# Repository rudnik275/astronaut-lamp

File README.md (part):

# Лампа-космонавт → нативное устройство Apple HomeKit

Ночник «космонавт на луне» + звёздный проектор (Rozetka 566431028, AURA_HUB, ~530 грн).
Куплен и разобран 2026-08-23. **Решение: выкидываем ИК-пульт и родной контроллер,
внутрь ставим ESP32-WROOM-32 с прошивкой HAA — лампа появляется в Apple Home как
настоящая цветная LED-лампа + отдельный выключатель проектора, без хабов и мостов.**

## Статус на 2026-09-05 (точка входа для новой сессии)

- ✅ **ESP32 прошит HAA 12.18.1 (04.09)** и **спарен с Home.app**. Чип ESP32-D0WD-V3,
  порт `/dev/cu.usbserial-120`, точка доступа setup-режима `HAA-620DA0`, код спаривания
  `0218-2017`. Имена в Home.app: аксессуар «Космонавт», лампа «Цвет неба», мотор
  «Движение неба». Уровни на GPIO проверены мультиметром: 25 = R, 26 = G, 27 = B, 32 = мотор
- ✅ **С донора выпаяны и промерены** балласты `5R6` (R) и 2× `3R3` (G, B) **плюс `6R8` (R18)**
  из цепи мотора — на доноре мотор шёл `MD → D1 → 6R8 → Q1`, а не напрямую (§1, §3).
  Гнёзда `RGB`/`MD` оказались SMD с шагом 2.0 мм: вилки с кабелей срезаны, кабели теперь
  с голыми концами, провода светодиода опознать по фото вилок
- 📐 **Схема, таблица соединений для breadboard, порядок работ и раскладка в корпус:**
  `docs/schematic.html` (та же страница опубликована как артефакт, ссылка в памяти сессии).
  Конфиг HAA, залитый в плату: `docs/haa-config.json`. Размеченное фото донора:
  `photos/board-XKD1621-desolder.jpg`
- 🔧 **Монтаж на перфборде (08.09):** `docs/wiring.html` — карта 14 проводов (пин ESP32 →
  отверстие), раскладка по отверстиям платы 10 × 24 (вид сверху и зеркальный вид снизу),
  правила пайки на перфборде, порядок сборки, чеклист. Раскладка: TO-220 плашмя, ноги в ряд H,
  резисторы стоя в рядах I–J, шина GND голым проводом по ряду G снизу, шина +5 по ряду I
  в колонках 21–24, C1 на боку в колонках 21–24, D1 в `I20–I21`. 10 кОм стоит со стороны GPIO
  от 220 Ом (эквивалентно схеме). Плата берётся целиком, 25.4 × 61 мм после обрезки полей —
  отсек ранца считать под неё, а не под 24 × 58. Связи раскладки проверяются скриптом на
  самой странице (18 цепей, замыканий и разрывов нет)
- 🖨️ **Печатная плата astro-driver v1 (09.09):** `hardware/` — проект KiCad 10 с ESP32-WROOM-32E
  на плате, USB-C (питание + прошивка через CH340C), пять ключей AO3400A (R, G, B, мотор,
  лазер на GPIO 33), выводные балласты 2 Вт и 1000 µF под ручную пайку. 60 × 47 мм.
  Схема и плата генерируются из `hardware/design.py` (`sh hardware/run.sh all`), нетлист
  схемы сверен с платой, DRC без электрических ошибок, 0 неразведённых. Гербер, BOM/CPL
  для сборки на JLCPCB, рендер и PDF схемы в `hardware/out/`. Цена: голые платы ~15–22 $
  за 5 шт, со сборкой SMD ~40–50 $ за 2 шт / ~55–70 $ за 5 шт (оценка, `hardware/README.md`).
  **На железе не проверено**, первая партия — прототип. Лазер в текущей ручной сборке
  висит параллельно мотору; на плате у него свой канал
- 🧩 **Корпус: печатаем новый ранец.** Отсек 63 × 52 × 20 мм, ESP32 со срезанной гребёнкой
  плашмя + полоска перфборда 24 × 58 рядом, один слой (раскладка в `docs/schematic.html`).
  Вход питания — **USB-C** вместо круглого: в корзине Али два кандидата с 5.1 кОм — на фланце
  (item 1005006939718172) и платка без фланца Choice (item 1005012148102188); 2-pin без CC
  и XH2.54 не брать (§4)
- ✅ **Драйвер спаян и работает (08.09):** перфборд по схеме §3 (своя раскладка), лампа
  и мотор управляются из Home.app. Лазер звёзд (разъём `JG` донора, §1) в параллель мотору
  через `R11` 10 Ом. **Решение 09.09: железо закрыто в таком виде**, пятый ключ, пересборка
  и печатная плата не делаются
- ⏭️ **Следующий и последний шаг:** конфиг HAA с эффектами (`"fx"`, плитки-выключатели
  эффектов), залить по Wi-Fi через режим настройки — [issue #3](https://github.com/rudnik275/astronaut-lamp/issues/3)
- 📄 Инвентарь деталей: Obsidian `справочники/электроника-инвентарь.md`; где покупать —
  `справочники/электроника-где-покупать.md` (там же USB-C гнёзда по трём магазинам)
- 🧭 Дальше по плану работ — §6

Связанные проекты: [nodemcu-co2](../nodemcu-co2/) (общий пул плат), Fusion/3D-печать
(держатель платы внутри основания — печатает друг, Bambu A1, PETG).

---

## 1. Что внутри (по фото разобранного основания)

Родная плата: **`XKD1621(733)`**, дата-код `231021`. Питание 5 В (пады `+5V` / `GND`
внизу справа), электролит 47 µF 16 V.

| Разъём / метка | Пины | Что это |
|---|---|---|
| `RGB` | 4: `V G R B` | **Аналоговый RGB-светодиод, общий анод** (`V` = +5 В). Ключи `Q2/Q3/Q4` (SOT-23) стоят по низкой стороне на R/G/B, рядом балласты `3R3`. |
| `MD` | 2 | Мотор звёздного проектора (`MD` = motor drive). Цепь по чистому фото (05.09): `MD → D1` (Шоттки `S4`) `→ R18 = 6R8 → Q1`. **Не Q5**, как думали по первому фото: `Q5` с `R11` (10 Ом) стоит у `J6`. |
| `JG` | 2 | **Лазер звёзд** (`JG` = 激光 jīguāng, лазер; раньше по фото ошибочно считали ИК-приёмником `J6`). Его драйвер: ключ `Q5` (SOT-23) + `R11` = `100` (10 Ом) последовательно + электролит `CE1` 47 µF. Уточнено 08.09.2026, когда после сборки не оказалось звёзд. Лазер полярный, в отличие от мотора. |
| `U2` | SOIC-16 | Родной контроллер: декодирует пульт, гонит ШИМ на Q2–Q4. Его и выбрасываем. |

**Ключевой вывод:** здесь **НЕ адресная лента (не WS2812B)**, а обычный RGB с общим
анодом на трёх ШИМ-каналах. Значит не нужны ни level shifter 3.3→5 В, ни DMA-пины,
ни ограничения WLED по GPIO. Задача сводится к «три ШИМ-канала + один ключ мотора».

Сам номер платы `XKD1621(733)` — это внутренний код китайского ODM-цеха, даташита нет
нигде и не будет (искали EN+ZH — ноль). Опознаём снизу вверх по функциям, и это не
проблема: схема этого класса ламп стандартна и совпала с референс-дизайнами
(Cmsemicon SC8F052 и подобные) пин-в-пин — «RGB-выходы active-low, общий анод, три
NPN/ключа по низкой стороне, 3-проводной ИК-приёмник». То есть наши догадки по фото
подтверждаются типовым дизайном.

### Что переиспользуем с платы, а что выкидываем

Ключевая мысль: **RGB-светодиод и мотор сидят на съёмных разъёмах** (белые JST на фото).
Их можно просто **отстегнуть от родной платы и воткнуть в свой драйвер на ноде** —
резать провода не обязательно.

| С платы | Решение |
|---|---|
| **RGB-светодиод** (разъём `RGB`, `V G R B`) | **Переиспользуем.** Это и есть свет лампы. `V` = общий +5 В анод. |
| **Мотор проектора** (разъём `MD`) | **Переиспользуем.** Отдельный ключ = отдельный сервис в Home. |
| **Питание 5 В** (родной адаптер → пады `+5V`/`GND`) | **Переиспользуем**, если адаптер тянет (проверить ток, см. §5). |
| Корпус, крепления, JST-разъёмы | **Переиспользуем.** |
| **U2** (16-pin) — родной мозг/ИК-декодер | **Выкидываем**, его роль берёт NodeMCU. |
| **J6** (3 пина) — ИК-приёмник | **Не нужен**, управление по Wi-Fi. |
| Q2/Q3/Q4 (ключи RGB), Q5 (ключ мотора) | **Опционально** — см. две стратегии ниже. |

**Стратегия A — свой драйвер (выбрана и реализована).** Родную плату не трогаем
вообще: отстёгиваем разъёмы `RGB` и `MD`, ведём их в свой маленький драйвер на 4
logic-level MOSFET (схема в §3). *Поправка 04.09: гнёзда на плате оказались SMD с шагом
2.0 мм, dupont в вилки не входит, поэтому вилки с кабелей срезаны и кабели идут в драйвер
голыми концами. С платы сняты только четыре резистора: `5R6`, 2× `3R3`, `6R8`.* Плюс: полностью известная схема, никакой пайки SOIC.
Минус: докупить 4 транзистора (копейки).

**Стратегия B — переиспользовать родные ключи (экономит детали).** Выпаять U2 и
подать ШИМ с ноды прямо на входы Q2/Q3/Q4/Q5 (через их же базовые/затворные резисторы).
Плюс: 0 новых деталей. Минусы: надо выпаять 16-ногую SOIC (лучше феном) и прозвонить,
какая нога куда шла; работает чисто, **если** ключи — это NPN-биполярники (для 5-В лампы
очень вероятно, референс использует S8050) или logic-level MOSFET. Если это MOSFET с
высоким порогом — от 3.3 В не откроются, тогда всё равно Стратегия A.

**Как выбрать за 2 минуты мультиметром:** посмотреть на вход Q2. Резистор ~1 кОм в
управляющую ногу = биполярник (Стратегия B безопасна). Голый затвор + подтяжка вниз =
MOSFET (проверить порог). Не хочешь возиться — бери Стратегию A.

**Стратегия C — ИК-инъекция (идея Димы): плату не трогаем вообще, выбрасываем ИК-приёмник
и подаём сигнал с ESP прямо на его пин.** Разобрана отдельно в §2.5. Электрически чисто и
это самый быстрый путь, но платой управляет по-прежнему родной U2, а он понимает только
язык пульта — поэтому в Home.app получится не лампа, а набор кнопок. Подробности и
цифры — там же.

### Сравнение трёх стратегий

| | Что делаем | Цвет в Home.app | Яркость | Состояние | Цена |
|---|---|---|---|---|---|
| **A. Свой драйвер** | 4 MOSFET на макетке, ESP рулит светодиодом напрямую | **любой, цветовой круг** | **плавно 0–100 %** | **точное** | 4 транзистора + час пайки |
| **B. Убить U2** | выпаять SOIC-16, ШИМ с ESP на базы родных ключей | **любой, цветовой круг** | **плавно 0–100 %** | **точное** | фен + прозвонка, 0 покупок |
| **C. ИК-инъекция** | один провод в разъём `J6`, ESP притворяется пультом | только **16 пресетов** | только ступеньками `±` | **вслепую** | один провод |

**Рекомендация: A** (или B, если любишь паять и не хочешь ничего покупать). Стратегия C
даёт «умную лампу» в кавычках — ровно то, от чего отказались в самом начале, просто
без ИК-светодиода.

---

## 2. Архитектура (выбрана)

**NodeMCU V3 (ESP8266) + прошивка HAA (Home Accessory Architect, RavenSystem).**

HAA — единственная живая прошивка с **нативным HomeKit на ESP8266** (последний релиз
v12.18.1 «Merlin», 2026-07-26). Лампа регистрируется в Home.app **как настоящий
HomeKit-аксессуар: без Home Assistant, без Homebridge, без NAS и без моста**.
Поддерживает ровно нашу схему: Lightbulb с ШИМ-каналами `"g":[R,G,B]`, плюс вторым
сервисом Switch на мотор проектора.

⚠️ **Бинарники лежат в репозитории `RavenSystem/haa`, а не в `esp-homekit-devices`** —
у второго в релизах вообще нет файлов, только changelog. Проверено 2026-08-23: в релизе
12.18.1 лежит 80 ассетов, ESP8266-сборки — это файлы **без суффикса** `_esp32*`
(`fullhaaboot.bin`, `haamain.bin`, `otamain.bin`). Сборки живые, не остатки: размер
`haamain.bin` меняется от релиза к релизу, и заголовок `fullhaaboot.bin` — настоящий
ESP8266-образ (magic `0xE9`, точка входа `0x401008dc` в IRAM ESP8266).

- Релизы (бинарники): https://github.com/RavenSystem/haa/releases
- Wiki Lightbulb: https://github.com/RavenSystem/esp-homekit-devices/wiki/Lightbulb
- Wiki GPIO: https://github.com/RavenSystem/esp-homekit-devices/wiki/GPIOs-Configuration
- Wiki установки: https://github.com/RavenSystem/esp-homekit-devices/wiki/Installation

### Честно про риски ESP8266 (перепроверка 2026-08-23)

Плана это не ломает, но знать надо:

- **ESP8266 у HAA в режиме «поддерживаем, но не развиваем».** Все новые фичи идут только
  под ESP32 (HTTPS, MQTT, хардварный ШИМ, ADC-режимы). Автор прямым текстом в issue #2407:
  Wi-Fi-драйвер закрытый, а **SDK под ESP8266 Espressif забросил** (последний
  ESP8266_RTOS_SDK v3.4 — апрель 2021), поэтому баги Wi-Fi-слоя он починить не может.
- **Сам чип ESP8266EX — NRND с ноября 2025** (не рекомендован для новых разработок).
- Был реальный регресс в 2026: на 12.16 часть ESP8266-устройств отваливалась (issue #2408),
  закрыт как невоспроизводимый после 12.17.
- **Вывод:** для этой лампы ESP8266 берём осознанно — плата уже есть, задача простая
  (3 ШИМ + бинарный выход). Если бы железо покупалось с нуля — брал бы ESP32-C6.

### Прошивка HAA: конкретика

> ⚠️ **Секция историческая — писалась под ESP8266, до смены платы.** Номера GPIO
> (5/4/14/12), режим ШИМ `7` и команды esptool с `-fs 1MB -fm dout` здесь НЕ для
> нашего ESP32. Актуальное: пины и конфиг — §3, команды прошивки ESP32 — §6.
> Общие вещи (массив `"io"` обязателен, `"es"`-группировка, initial value) верны для обеих плат.

**Мотор делаем БИНАРНЫМ выходом, а не ШИМ.** Это важно: софтверный ШИМ на ESP8266
ограничен **2000 Гц** (дефолт 305 Гц), и мотор на такой частоте будет слышимо пищать.
Нам скорость вращения регулировать не надо — только вкл/выкл, поэтому проблемы нет.
Если позже захочется «медленное вращение» — это аргумент за ESP32 (там хардварный ШИМ
до 29 кГц), на ESP8266 будет писк.

**Лимит, который надо помнить:** одна служба Lightbulb принимает **максимум 5 ШИМ-каналов**
(в исходниках `uint8_t gpio[5]`). Наши R/G/B — три, всё ок, но мотор четвёртым каналом
лампы сделать нельзя даже при желании — только отдельным сервисом. Мы так и планировали.

**ШИМ НЕ инвертируем.** Общий анод + N-ключ по низкой стороне = «единица на затворе»
означает «горит», это нормальный режим (`PWM mode 0` — дефолт). Но **осознанно задать
initial value**, иначе на старте лампа может вспыхнуть на полную до инициализации службы.

Скелет конфига (R/G/B на GPIO 5/4/14, мотор на GPIO 12). Обязателен массив `"io"` —
без него GPIO просто не включатся, это самая частая ошибка новичка:

```json
{
  "c": { "io": [ [[5,4,14], 7], [[12], 2] ] },
  "a": [ {
    "t": 30,
    "g": [5,4,14],
    "es": [ { "t": 1, "0": {"r":[[12,0]]}, "1": {"r":[[12,1]]} } ]
  } ]
}
```

`"c"` — общие настройки, `"a"` — массив аксессуаров, `"es"` — дополнительные службы
внутри аксессуара (так экономится RAM и всё группируется одной плиткой в Home.app).
Режим GPIO `7` = софтверный ШИМ-выход, `2` = бинарный выход. `"t":30` = Lightbulb,
`"t":1` = Switch. Точные ключи сверить по wiki перед заливкой.

**Команды прошивки** (плата 4 МБ, но образ собран под 1 МБ — флаг `-fs 1MB` правильный,
«помогать» флагом `4MB` не надо; GPIO0 на GND для входа в режим прошивки):

```
python3 -m esptool flash_id
python3 -m esptool erase_flash
python3 -m esptool -b 115200 --before=default_reset --after=hard_reset write_flash -fs 1MB -fm dout 0x0 fullhaaboot.bin
```

В Home.app будет предупреждение «непроверенный аксессуар» → **«Всё равно добавить»**.

В Home.app получится **один аксессуар с двумя сервисами**: «Космонавт» (цвет + яркость)
и «Звёздное небо» (вкл/выкл, при желании — скорость вращения через ШИМ).

### Почему не альтернативы

| Путь | Вердикт |
|---|---|
| **HAA (выбран)** | Нативный HAP, нулевая инфраструктура, PWM RGB из коробки. Минус: конфиг — JSON («MEPLHAA script»), не такой привычный как YAML; спаривание на ESP8266 небыстрое. |
| ESPHome + Home Assistant на NAS + HomeKit Bridge | Полноценный план Б, живее чем казалось: в релизе **ESPHome 2026.1 (январь 2026) поддержку ESP8266 официально переподтвердили** («ESP8266 is no longer a platform we warn users away from»), интеграция в HA — Platinum. Минус прежний: тянет всегда-включённый NAS и мост, нативного HomeKit у ESPHome нет. Плюс: HA крутит свои автоматизации вообще без Apple-хаба. В Docker нужен `network_mode: host` (иначе mDNS не пролезет). |
| WLED | Нативного HomeKit нет вообще, и он про адресные ленты — у нас их нет. Мимо. |
| HomeSpan | Только ESP32. NodeMCU V3 не подходит. |
| Оставить ИК и подменять пульт | Отменено пользователем — хотим настоящее устройство, а не эмуляцию кнопок. |
| **Aqara Hub M3** (встроенный ИК-бластер) | Не отменяет план — см. ниже. Даёт ту же «эмуляцию кнопок», от которой отказались, и лампой-с-цветовым-кругом она в Home.app не станет. |

### Про Aqara Hub (и любой хаб): ноду он в HomeKit НЕ заведёт — и не нужен

Путь «NodeMCU → Apple HomeKit **через Aqara Hub**» не работает, причём по двум
независимым причинам сразу (перепроверено 2026-08-23):

1. **Со стороны ноды.** У ESP8266 нет ни Zigbee, ни Thread (802.15.4-радио в нём
   физически отсутствует — даташит ESP8266EX), ни Matter. Причём Matter — это не
   «пока не портировали»: порта `ESP8266` в `connectedhomeip` не существовало никогда,
   и все три стека живут в ESP-IDF, для которого ESP8266 вообще не является таргетом.
2. **Со стороны хаба — и это добивает.** Aqara-хаб бриджит **только устройства самой
   Aqara**. Даже чужой *Zigbee*-девайс он не примет: официальный ответ поддержки Aqara
   (форум, 2025) — «the hub currently supports only Aqara Zigbee devices and not
   third-party Zigbee ones», у них это даже в названиях товаров на Amazon написано
   («Features Aqara Zigbee (Not Third-Party)»). Третьесторонние устройства у M3/M100/M200
   принимаются **только по Matter**.

То есть даже гипотетический «привинтить к ноде Zigbee-модуль» не спас бы. Звена
«нода → Aqara → HomeKit» не существует ни в каком виде.

**И хаб для этого не нужен.** Прошивка **HAA** делает саму ноду **нативным
HomeKit-аксессуаром прямо по Wi-Fi** — лампа появляется в Home.app напрямую, без всякого
моста. Это меньше звеньев и надёжнее любого хаба: локальное управление с айфона.
HomePod/Apple TV — как и для любого HomeKit-устройства — нужен только для автоматизаций
по расписанию и доступа извне, но не для того, чтобы лампа работала дома.

Если хочется задействовать уже купленный Aqara-хаб — **эту лампу он не потянет**, это
мост не того типа. Хаб пусть остаётся под датчики Aqara / Zigbee / кондиционер.

> Если бы стояла ESP32 (а не ESP8266), появился бы Matter — но и тогда устройство
> правильнее сдавать **напрямую** в Apple Home, а не гонять через Aqara. На нашей ноде
> вопрос закрыт: HAA, напрямую по Wi-Fi.

⚠️ HomeKit-аксессуар спаривается **только с одним контроллером**: либо Apple Home,
либо Home Assistant. Выбираем Apple Home.

⚠️ **Хаб**: управление с iPhone в той же Wi-Fi работает без хаба. Для автоматизаций
(«включить на закате»), Siri вне дома и удалённого доступа нужен HomePod / Apple TV.
Поддержка iPad как хаба закончилась 2026-02-10.

⚠️ ESP8266 — **только 2.4 ГГц Wi-Fi**. На роутере должен быть доступен 2.4-ГГц SSID.

---

## 2.5 Стратегия C: ИК-инъекция в пин приёмника — разбор

**Идея:** родную плату не переделываем совсем. Выбрасываем ИК-приёмник, а на его
сигнальный пин (разъём `J6`) подаём с ESP тот же цифровой сигнал, который выдавал бы
приёмник, — U2 думает, что нажали кнопку на пульте. Идея рабочая, приём известный,
и разъём `J6` делает её обратимой без единого разреза: приёмник просто **отстёгивается**.

### Электрическая часть — тут всё сходится

Выход ИК-приёмника (VS1838B / TSOP-класс) — **открытый коллектор с внутренней подтяжкой
~30 кОм**, покой = **HIGH**, приём пачки = **LOW** (подтверждено даташитами Vishay и Sivago).
Значит с ESP надо выдавать **инвертированную огибающую без несущей**: покой HIGH,
9000 мкс LOW, 4500 мкс HIGH, дальше биты 560 мкс LOW + (560 = «0» / 1690 = «1»), 32 бита,
хвост 560 мкс LOW. Это протокол NEC, 38 кГц — у этих ламп он практически всегда.

Два важных следствия:

- **Пин ESP настраивать как open-drain, а не push-pull.** Тогда ESP только «тянет вниз»,
  а HIGH формирует подтяжка от 5 В самой платы → U2 видит честные 5 В, и вопрос
  «прочитает ли 5-вольтовый вход наши 3.3 В» **снимается полностью**. Иначе он вполне
  реален: для 5-В CMOS порог V_IH = 3.5 В, а у нас 3.3 В — не проходит.
- ⚠️ **Раз приёмник выбрасываем — вместе с ним уходит его подтяжка 30 кОм.** На дешёвых
  платах своей часто нет. **Померить линию `J6` после снятия приёмника**: если висит в
  воздухе — впаять 4.7–10 кОм на +5 В, иначе U2 будет ловить мусор.

Прецеденты есть, приём описан: ctuck (10-Вт RGB-прожектор, 44-кнопочный пульт),
Wolfgang Ziegler, тред на All About Circuits, ESPHome-проект Daikin.

### HAA это умеет, но через недокументированную дверь

HAA шлёт ИК действием `"i"` внутри аксессуара. Проблема: по умолчанию он выдаёт
**модулированную несущую 38 кГц** — для ИК-светодиода. Нам нужна **несущая выключенной**,
иначе U2 увидит не чистый LOW, а дребезг.

Разбор исходников v12.18.1 (`irrf_tx_task()`): при `freq <= 1` HAA переключается на
«RF-путь» и выдаёт **ровный уровень без несущей** — ровно то, что надо. Но:

- включается это **только глобально**, через `"x": 500` (внутри считается `1000/500/2 = 1`).
  `"x": 0` **нельзя** — деление на ноль;
- пин и инверсия задаются **недокументированными ключами** `"g"` (GPIO) и `"k"` (инверсия),
  в wiki их нет вообще;
- разбор `"x"` срабатывает, только если объявлен ещё и `"t"` — нужен **фиктивный** `"t"`
  на неиспользуемый пин, иначе молча вернётся 38 кГц;
- задать несущую по-действию (`"x":1` внутри `"i"`) **не выйдет** — код это значение
  отбрасывает.

⚠️ Всё это выведено **чтением исходников, а не проверено на стенде**. Запасной вариант,
полностью документированный, — не выбрасывать приёмник, а приклеить напротив него
ИК-светодиод и светить в упор. Но раз приёмник выбрасываем, этот запасной путь закрыт.

**Коды надо снять со своего пульта.** У WLED в базе шесть разных вариантов
24-кнопочных пультов — клоны отличаются, чужим таблицам верить нельзя. В HAA есть
захват (только в Setup Mode), причём **можно ловить прямо с линии родного приёмника**,
пока он ещё на месте, — отдельная железка не нужна. Снять коды надо **до** того, как
приёмник выброшен.

### Чем за это платим — главное

Управлять лампой продолжает **родной U2**, а он понимает только язык пульта:

- **Цвет — только фиксированная палитра**, 16 кнопок у 24-клавишного пульта (20 у
  44-клавишного). Произвольного RGB нет: команды «выставь #A3F0C1» в пульте не существует.
- **Яркость — только относительная**, кнопками `+`/`-` (~16 ступеней). **Абсолютной команды
  нет ни в одном наборе кодов.** HomeKit присылает «поставь 42 %», а мы можем только
  «нажать минус N раз» вслепую. Хуже: в динамических режимах те же кнопки превращаются
  в регулятор скорости — перед яркостью надо всегда сначала слать статичный цвет.
- **Обратной связи нет вообще.** Состояние держим в уме; после моргания питания U2
  сбрасывается в своё, а плитка в Home.app продолжает врать.
- **И самое неприятное для HomeKit:** у HAA wildcard-действия для Lightbulb есть **только
  по яркости** (`"y0"`), **по оттенку — нет**. То есть цветовой круг Home.app к палитре из
  16 кнопок привязать нечем. Придётся делать либо N отдельных выключателей, либо
  сервис TV со списком «входов» как палитрой.
- Хорошая новость по кнопке питания: у 24-клавишных пультов **ON и OFF — раздельные
  команды**, значит выключение идемпотентно и состояние хотя бы не уплывает по питанию.
  У 44-клавишных питание — один тумблер, и вот там состояние поплывёт неизбежно.
- Мотор проектора управляется только если под него есть кнопка на пульте — иначе к нему
  всё равно тянуть провод.

**Итог: в Home.app получится не лампа, а пульт в виде плиток.** Разница с вариантом A —
четыре транзистора и час пайки.

## 3. Схема

### ⚠️ Плата: берём ESP32-WROOM-32 DevKit, а не NodeMCU V3

Решение изменено 2026-08-23 после проверки. Причина одна и она по существу задачи:
**у ESP8266 вообще нет аппаратного ШИМ.** HAA на нём умеет только программный ШИМ с
потолком 2000 Гц (по умолчанию 305 Гц), который крутит сам процессор — а мы просим
три канала одновременно, пока рядом работают Wi-Fi и HomeKit. Это прямой риск мерцания
и дёрганой яркости, то есть ровно той функции, ради которой всё делается.

У ESP32 это аппаратный блок **LEDC**: 8 каналов, 4 таймера, **1 Гц – 29 кГц**
(в HAA — режим GPIO `9`, дефолт 5 кГц). Яркость держится железом и firmware-нагрузке
безразлична. Бонусом NodeMCU V3 остаётся свободной под CO2-монитор, как и планировалось.

**ESP32-C3 SuperMini (тот, что 150 грн) — не брать.** У него два подтверждённых дефекта:
керамическая антенна CA-C03 поставлена без зазора и платы просто не подключаются к
Wi-Fi на полной мощности передатчика (замеры sigmdel на 4 платах: 1250 мс против 50 мс
после снижения TX power), плюс на части партий стоит LDO на 250 мА при пиках чипа до
335 мА. В пластиковом основании рядом с коллекторным моторчиком это лишняя лотерея.

### Схема

```
   5 В от родного адаптера
        │
        ├──► ESP32 DevKit, пин VIN/5V   (GND — общий со всем)
        │
        ├──► пин V разъёма RGB          (общий анод светодиода)
        │
        └──► + мотора проектора
                                         ESP32-WROOM-32
   RGB.R ──[5R6]──► сток Q_R ──┐         GPIO25 ──[220 Ω]──► затвор Q_R
   RGB.G ──[3R3]──► сток Q_G ──┼─ исток  GPIO26 ──[220 Ω]──► затвор Q_G
   RGB.B ──[3R3]──► сток Q_B ──┤  на GND GPIO27 ──[220 Ω]──► затвор Q_B
   мотор ──[6R8]──► сток Q_M ──┘         GPIO32 ──[220 Ω]──► затвор Q_M

   [5R6]/[3R3] — балласты каналов, снятые с родной платы XKD1621; привязка к цветам
   подтверждена прозвонкой донора 04.09.2026 (5R6 = R, 3R3 = G и B).
   [6R8] — R18 с той же платы, стоял последовательно с мотором; без него мотор получит
   все 5 В и будет крутиться быстрее задуманного.
   Полная схема с таблицей соединений и пинаутами: docs/schematic.html
```

- ⚠️ **БАЛЛАСТНЫЕ РЕЗИСТОРЫ СВЕТОДИОДА — НЕ ЗАБЫТЬ (ревизия 2026-08-24).** Токоограничение
  каналов R/G/B живёт **на родной плате** (SMD `3R3` = 3.3 Ом и `5R6` = 5.6 Ом рядом с
  Q2/Q3/Q4), а не в модуле светодиода. Если воткнуть светодиод в наш драйвер без них —
  ток через кристаллы ничем не ограничен, и ШИМ не спасает (ШИМ режет среднее, а убивает
  пиковый ток). **В каждый канал последовательно нужен балласт**: либо выпаять родные
  `3R3`/`5R6` с платы `XKD1621` и перенести на макетку (бесплатно и номиналы ровно те —
  `5R6` скорее всего красный канал, `3R3` — зелёный/синий), либо купить резисторы
  3.3–5.6 Ом **мощностью 2 Вт** (на ~0.5 А через 3.3 Ом рассеивается ~0.8 Вт, обычный
  0.25 Вт сгорит). Итоговый номинал подобрать после замера тока из §5.
- На каждый затвор: **220 Ω** последовательно + **10 kΩ подтяжка к GND — обязательно**.
  До того как HAA сконфигурирует пины (сотни мс после старта), все GPIO висят в воздухе,
  и без подтяжки состояние лампы и мотора при каждой загрузке непредсказуемо.
  (100 Ω было бы каноничнее, но во Всеплюсе его нет, а 220 Ω для наших частот — то же самое.)
- Через мотор — **обратный диод 1N5819** катодом к +5 В, иначе выброс убьёт ключ.
- По питанию 5 В — **1000 µF** электролит рядом с платой.
- ШИМ **не инвертированный**: общий анод + N-ключ по низкой стороне, «затвор в 1» = горит.

**Выбор GPIO не случайный.** У ESP32 нельзя трогать: `0, 2, 5, 12, 15` (strapping —
плата не загрузится или выберет не то напряжение флеша), `6–11` (флеш), `1, 3` (UART0,
на них сыплется лог загрузки), `34–39` (только вход). Пины `25/26/27/32` чистые.

Конфиг HAA под эту схему — аппаратный ШИМ, мотор простым выходом:
`"io":[[[25,26,27],9,0,0,0,0],[[32],2,0,0]]` (точную сигнатуру `io`-массива сверить по
wiki перед заливкой). `"y":[1000]` можно вообще опустить — дефолт аппаратного ШИМ 5 кГц,
он только глаже.

**Опция после смены платы (ревизия 2026-08-24): мотору можно дать СКОРОСТЬ.** Правило
«мотор — только бинарный выход» пришло из эпохи ESP8266 (софт-ШИМ ≤2 кГц = слышимый писк)
и на ESP32 устарело: аппаратный LEDC тянет 20+ кГц — выше слышимого диапазона, мотор
не пищит. То есть GPIO32 можно сделать ШИМ-каналом и отдать «Звёздное небо» в Home.app
Fan-сервисом с регулировкой скорости вращения (код типа сервиса — по wiki). Бинарный
вкл/выкл проще и остаётся дефолтом; скорость — бесплатный апгрейд, если захочется
«медленное небо». Железо одно и то же, меняется только конфиг.

**MOSFET-ы обязательно logic-level** (открываются от 3.3 В): `IRLZ44N` (TO-220, удобно
паять руками, с большим запасом) или `AO3400A` (SOT-23). ❌ **Не брать `IRF540`** и
готовые модули на нём — порог затвора до 4 В, от 3.3 В он толком не откроется.

---

## 4. Что купить — корзина Всеплюс (проверено 2026-08-23)

**Магазин: `vseplus.com`.** Проверялись оба, РКС отпадает: там нет в наличии ни NodeMCU,
ни ESP32 DevKit (только WeMos D1 mini и ESP32-C6 в количестве 2 шт), а JST на 3 и 4 пина
идут с минималкой 500–1000 шт под заказ. Всеплюс закрывает весь список одним заказом.
Цены — «специальная» (по лояльности) там, где магазин показывает две.

| Позиция | Зачем | Кол-во | Грн | Ссылка |
|---|---|---|---|---|
✅ **Корзина собрана на сайте 2026-08-23, фактическая сумма — 656 грн.** Расхождение с
расчётными 530 объясняется двумя вещами, обе выяснились только при оформлении:
**у магазина есть минимальные партии** (диоды — от 10 шт, макетка — от 2 шт) и
**«спец. ціна» не действует на первый заказ** — она даётся после двух оплаченных,
а я считал по ней. Ниже колонка «Грн» — фактическая, за всю позицию.

| Позиция | Зачем | Кол-во | Грн | Ссылка |
|---|---|---|---|---|
| Плата розробника **ESP32-WROOM-32** | мозг | 1 | **265** | [ссылка](https://vseplus.com/ua/product/plata-rozrobnika-esp32-wroom-32-553955) |
| Транзистор **IRLZ44NPBF** (TO-220) | 3 канала цвета + мотор | 4 | **248** | [ссылка](https://vseplus.com/ua/product/tranzistor-polovij-n-kanalnij-irlz44npbf-128604) |
| ~~Резистор 220 Ом~~ | ✅ **есть, 20 шт** (`CF1/4W-220R`) | — | — | — |
| ~~Резистор 10 кОм~~ | ✅ **есть, 10 шт** (`MFR100SSFTB-10KR`, 1 Вт — крупные, но рабочие) | — | — | — |
| Діод **1N5819** | обратный на мотор | **10** (мин. партия) | **40** | [ссылка](https://vseplus.com/ua/product/diod-1n5819-127851) — Шоттки, DO-41, 40 В, 1 А |
| Конденсатор **1000 мкФ 16 В** | по питанию | 1 | **17** | [ссылка](https://vseplus.com/ua/product/kondensator-elektroliticnij-vividnij-90291) — номинал проверен: 1000 uF / 16 V / 105 °C |
| **Макетна плата 3×7** двостороння | на неё паяем драйвер | **2** (мин. партия) | **86** | [ссылка](https://vseplus.com/ua/product/maketna-plata-3x7-dvostoronna-zelena-122222) — 30×70 мм |
| ~~Макетна плата 400 контактів~~ | ✅ **уже есть у Димы** | — | — | — |
| ~~Dupont тато-мама / тато-тато~~ | ✅ **есть, по ~40 шт каждого** | — | — | — |
| ~~Провід монтажний 24AWG~~ | ✅ **есть** (катушка почти пустая, добить по остатку) | — | — | — |
| ~~Обплетення Pro'sKit 8PK-031A~~ | ✅ **есть** (не попала на фото) | — | — | — |
| | | **Итого** | **656 грн** | |

📦 **Заказ получен 03.09.2026** (накладная № 49044674 от 27.08.2026). Позиции
пересчитаны по накладной и сошлись с таблицей выше. Той же поставкой пришла вторая
накладная на 354 грн — крепёж, 100× резистор 330 Ом 0.25 Вт и электролит 470 мкФ 35 В;
к этому проекту она не относится, но лежит в общем пуле (см. инвентарь).

📦 **Инвентарь того, что уже есть, ведётся в Obsidian:**
`справочники/электроника-инвентарь.md` (составлен 2026-08-23 по фото). Сверяться перед
любой закупкой. Вычеркнутые строки выше — оттуда.

### Плата: решено брать ESP32 сразу (Дима, 2026-08-23)

Вариант «собрать на своей NodeMCU и посмотреть, мерцает ли» **отклонён** — берём ESP32
без промежуточного шага. Обоснование то же, что в §3: аппаратный ШИМ (LEDC) снимает риск
мерцания конструктивно, а не «на глаз», и не придётся потом перепаивать.

Обе NodeMCU (их у Димы две — разные USB-чипы `CH340` и `CP2102`) остаются свободными:
одна под [[птичка-co2]], вторая в запас.

**Чего в закромах не нашлось совсем:** ни одного MOSFET, ни конденсаторов, ни диодов
россыпью, ни перфборда, ни оплётки. Симисторы `BT136-600E` и твердотельные реле
`G3MB-202P`, которые есть, **для этой задачи не годятся** — они про коммутацию 220 В
переменного тока, а нам нужен низковольтный DC и плавный ШИМ.

**Опционально:**

| Позиция | Когда нужно | Грн | Ссылка |
|---|---|---|---|
| Набір роз'ємів **XH2.54** | если родные JST не переживут выпайку | 165 | `/ua/product/nabir-rozemiv-xh254-90103` |
| ~~БЖ 5V 2A~~ | ✅ **не нужен — у Димы есть USB 5 В 2 А** | — | — |
| Відсмоктувач припою **ZD-808** | если оплётки мало | 216 | `/ua/product/vidsmoktuvac-pripou-zd-808-209446` |

### Сравнение с РКС: дробить заказ не стоит (кроме одного случая)

Считано 2026-08-23 **с НДС** — это принципиально: у РКС на сайте **по умолчанию включён
режим «Ціна без ПДВ»**, и их ценники выглядят на 20 % привлекательнее, чем есть на самом
деле. Всеплюс показывает финальную цену. Плюс у РКС на мелочёвке минималки: резисторы —
от 30 шт, диоды — от 10, конденсаторы — от 5.

| Позиция | Всеплюс | РКС (с ПДВ) | Кто дешевле |
|---|---|---|---|
| Плата ESP32-WROOM-32 | **265** | нет в наличии | **только Всеплюс** |
| IRLZ44N ×4 | **208** | 216 | Всеплюс (паритет) |
| Резистор 10 кОм | **2** (5 шт) | 25 (мин. 30 шт) | **Всеплюс** |
| Резистор в затворы | **8** (220 Ом, 5 шт) | 25 (100 Ом, мин. 30 шт) | Всеплюс по деньгам, РКС по номиналу |
| 1N5819 ×2 | **6** | 24 (мин. 10 шт) | **Всеплюс** |
| Конденсатор 1000 мкФ | **14** | 24 (мин. 5 шт) | **Всеплюс** |
| Dupont тато-мама | **35** | 90 | **Всеплюс** |
| Dupont тато-тато | **35** | 42 | Всеплюс |
| Провід монтажний | **17** | 26 | Всеплюс |
| Перфборд 3×7 | 35 (1 шт) | **26** (2 шт, мин. 2) | **РКС** — вдвое больше и дешевле |
| Breadboard | 82 (400 конт.) | **67** (BB-801) | **РКС** |
| Оплётка | 94 (Pro'sKit) | **42** (ZD-180 1 мм) | **РКС**, вдвое |
| Відсмоктувач (опц.) | 180 (ZD-809T) | **96** (тот же ZD-809T) | **РКС**, вдвое |

**Вывод: всё берём во Всеплюсе.** Выигрыш от разделения — около **76 грн**, и он целиком
съедается второй доставкой Новой Почтой (~70–90 грн; ни один из магазинов не публикует
порога бесплатной доставки). Плюс у РКС нет наложенного платежа — только предоплата и
обязательная регистрация, тогда как Всеплюс принимает післяплату.

**Единственное исключение — самовывоз.** У РКС есть точка в Киеве:
**РАДІОМАГ, вул. Ушинського, 1** (Пн–Сб 9:00–16:00, закрыто во время тревог).
Всеплюс — только отправка, склад в Ровно, самовывоза нет вообще. Если едешь мимо
Ушинского, имеет смысл разделить так:

- **РКС, самовывозом:** оплётка 42 + отсос 96 + 2 перфборда 26 + breadboard 67 = **231 грн**
  (те же позиции во Всеплюсе — 391 грн, и без отсоса)
- **Всеплюс, доставкой:** плата, транзисторы, резисторы, диоды, конденсатор, dupont,
  провод = **590 грн**

Итого ≈ 820 грн, но с отсосом и лишней макеткой в комплекте, и доставка одна.

**Чего во Всеплюсе нет / что не брать:**

- **Резистор 100 Ом выводной не продаётся** — линейка прыгает с 47 Ом на 200 Ом.
  Берём 220 Ом, для затворов разницы нет.
- **Готовые MOSFET-модули не брать.** Единственный в наличии — на `IRF520`, а он **не**
  logic-level (нужно ~10 В на затвор, от 3.3 В толком не откроется). Модуль на AOD4184
  распродан. Берём дискретные IRLZ44N — они открываются от 3.3 В и по току в разы с запасом.
- **IRLB8721 не брать** — там он стоит 755 грн за штуку, это в 12 раз дороже IRLZ44N.
- **JST-PH 2.0 на 2/3/4 пина** — только кабели и переходники, отдельных разъёмов нет.
  Нам это неважно: родные разъёмы выпаиваем и переставляем.

ИК-светодиод, который планировался под старый путь, **больше не нужен**. Набор гнёзд
XH2.54 тоже: вилки с кабелей срезаны, в корпусе провода пойдут пайкой на перфборд.

### Вход питания — USB-C (решено 2026-09-05)

Раз корпус печатается заново, вместо круглого разъёма ставим гнездо USB-C. Требования:
гнездо на пластинке с двумя отверстиями под винт (окно в стенке + два М2) и **резисторы
5.1 кОм с CC1/CC2 на GND** — без них кабель C → C и любой PD-зарядник не дадут 5 В,
заработает только кабель A → C. В корзине Али (ещё не оплачено): 2 лота × 10 шт «Type-c Waterproof Female
Chassis Connector 16P with PCB Board Dual 5.1K», item `1005006939718172`, 116.51 грн/лот,
резисторы уже внутри. Запас идёт на [[птичка-co2]] и киндл-дашборд.
Вторая опция в той же корзине (05.09): платка без фланца «Type C Female … Dual 5.1K … 5/6Pin»,
item `1005012148102188`, 10 шт за 122.50 грн, Choice (доставка бесплатно). Электрически то же
самое, но держать её должен корпус: паз под платку 15 × 9 мм в стенке, окно под нос гнезда,
задний упор и прижим крышкой. Какой из двух типов ставить — решить, когда оба приедут. Украинские варианты
(РКС CR-24 5-pin, Всеплюс модуль 717836 + 5.1 кОм) — в `электроника-где-покупать.md`.
Потолок такого входа — 5 В × 3 А = 15 Вт; для ленты на 2 м нужен PD-триггер, не это гнездо.

---

## 5. Что замерить/уточнить перед сборкой

### ✅ ПРОВЕРЕНО 2026-08-23: ОБЩИЙ АНОД. Вопрос закрыт, корзина в силе

Тест A пройден: на обесточенной плате прозвонка между падом `+5V` и пином `V` разъёма
`RGB` **пищит** → `V` сидит на шине +5 В → светодиод с **общим анодом**.

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
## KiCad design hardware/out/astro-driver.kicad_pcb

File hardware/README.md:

# astro-driver v1 — печатная плата драйвера лампы-космонавта

ESP32-WROOM-32E прямо на плате, USB-C для питания и прошивки, пять ключей (R, G, B,
мотор, лазер), посадочные места под выводные балласты 2 Вт и электролит 1000 µF.
Плата 60 × 47 мм, двухслойная, антенна модуля свисает за верхний край на 3 мм.
Проект KiCad 10 **генерируется скриптами** из одного описания (`design.py`): и схема, и
плата рождаются из одного списка цепей, и их совпадение проверяется автоматически.

## Что в папке

| Файл | Что это |
|---|---|
| `design.py` | детали (с кодами LCSC для сборки на JLCPCB), цепи, координаты — единственный источник правды |
| `build_kicad.py` | плата: расстановка, цепи, контур, предразводка USB-C, зоны земли, BOM/CPL |
| `build_schematic.py` | схема на метках + сверка нетлиста схемы с `design.NETS` |
| `run.sh` | весь цикл: сборка → проверки → Freerouting → заливка → DRC → гербер/рендер/PDF |
| `lib/astro.pretty/` | копия посадочного места ESP32-WROOM-32 с courtyard по корпусу и отверстиями термопада 0.3 мм |
| `out/astro-driver.kicad_pro` `.kicad_sch` `.kicad_pcb` | проект: открывать в KiCad 10 (`~/Applications/KiCad/KiCad.app`) |
| `out/astro-driver-gerbers.zip` | гербер + сверловка для JLCPCB |
| `out/jlc-bom.csv`, `out/jlc-cpl.csv` | BOM и координаты для сборки (только SMD) |
| `out/astro-driver-schematic.pdf` | схема в PDF |
| `out/render-top.png`, `out/render-bottom.png` | рендер платы |

## Состояние

- Нетлист схемы = `design.NETS`: 36 цепей, расхождений нет.
- ERC: два предупреждения «power output ↔ power output» (V3 CH340C соединён с 3.3 В по даташиту — это норма для питания CH340C от 3.3 В).
- DRC после трассировки: 0 неразведённых связей, электрических нарушений нет. Остались
  косметические: шелкография модуля пересекает край платы (антенна свисает), пара
  наложений подписей.
- **Не проверено на живом железе.** Первую партию считать прототипом.

## Схема, коротко

- Питание 5 В с USB-C (площадка A4/B9, два контакта, до 2.5 А; вторая площадка VBUS
  намеренно пустая — между ними идут D+/D−/CC) или с разъёма `5V IN` от гнезда в стенке.
  CC1/CC2 через 5.1 кОм на землю, чтобы работал любой кабель и PD-зарядник.
- AMS1117-3.3 → 3.3 В для модуля и CH340C. Индикатор 3.3 В — красный светодиод.
- CH340C (без кварца) + два S8050 — автосброс EN/IO0 при прошивке, как на DevKit.
  Кнопки EN и BOOT выводные, необязательны.
- Каналы: GPIO25/26/27 → R/G/B, GPIO32 → мотор, GPIO33 → лазер. На каждом: 220 Ом в
  затвор, 10 кОм на землю, ключ AO3400A (SOT-23, logic-level, 5.7 А).
- Балласты выводные 2 Вт (`RR` 5R6, `RG`/`RB` 3R3, `RM` 6R8 мотор, `RL` 10R лазер), SS14
  параллельно мотору, 1000 µF по 5 В.
- Разъёмы 2.54 мм под пайку проводов или штыри: `J2` LED `V G R B` (порядок как на
  доноре), `J3` мотор (`1` ключ, `2` +5), `J4` лазер (`1` +5, `2` ключ — полярный!),
  `J5` 5V IN (`1` +5, `2` GND).

## Заказ на JLCPCB

1. jlcpcb.com → Order now → загрузить `out/astro-driver-gerbers.zip`. 2 слоя, 60 × 47 мм,
   5 шт (минимум), толщина 1.6, цвет любой, HASL. Остальное по умолчанию.
2. Включить **PCB Assembly**: Economic, Top side, 2 или 5 шт. Загрузить `jlc-bom.csv` и
   `jlc-cpl.csv`. В списке деталей проверить, что каждая позиция нашлась по коду LCSC и есть
   в наличии; при замене брать тот же корпус.
3. В предпросмотре расстановки **проверить поворот** ESP32, CH340C, AMS1117, USB-C,
   диода и светодиода: у KiCad и JLCPCB разные нулевые углы, JLCPCB даёт покрутить прямо
   в окне.
4. Выводные детали (балласты, электролит, гребёнки, кнопки) завод не ставит, паяются
   руками; они в BOM для сборки не входят.

Что не монтируется на заводе и нужно иметь: 2 Вт резисторы 3R3 ×2, 5R6, 6R8, 10R;
электролит 1000 µF 16 В; гребёнка 2.54 на 4 + 2 + 2 + 2 контакта (или просто провода);
две тактовые кнопки 6 × 6 (необязательно).

## Цена, ориентировочно (сентябрь 2026, проверить в калькуляторе JLCPCB)

| Вариант | Состав | Итого |
|---|---|---|
| Голая плата, 5 шт | плата ~2 $ + доставка в Украину 12–20 $ | **~15–22 $** за 5 плат, детали покупать и паять самому (модуль ESP32, CH340C, USB-C с шагом 0.5 мм — руками тяжело) |
| Со сборкой SMD, 2 шт | плата 2 $ + сборка 8 $ + два «extended»-компонента 6 $ + детали ~4.5 $/шт + доставка 15–25 $ | **~40–50 $** |
| Со сборкой SMD, 5 шт | то же + детали на 5 плат | **~55–70 $**, ~12 $ за плату |

Таможня не задевается: сумма ниже 150 €. Рекомендуется вариант со сборкой: всё сложное
паяет завод, дома остаются пять резисторов, конденсатор, гребёнки и провода.

## Пересобрать

```
sh hardware/run.sh all
```

Нужны: KiCad 10 в `~/Applications/KiCad/KiCad.app`, `brew install openjdk`, Freerouting jar
(`FREEROUTING_JAR=/путь/freerouting-2.4.1.jar`). Правки только в `design.py`; после
`run.sh all` смотреть строку «неразведённых связей» и DRC.

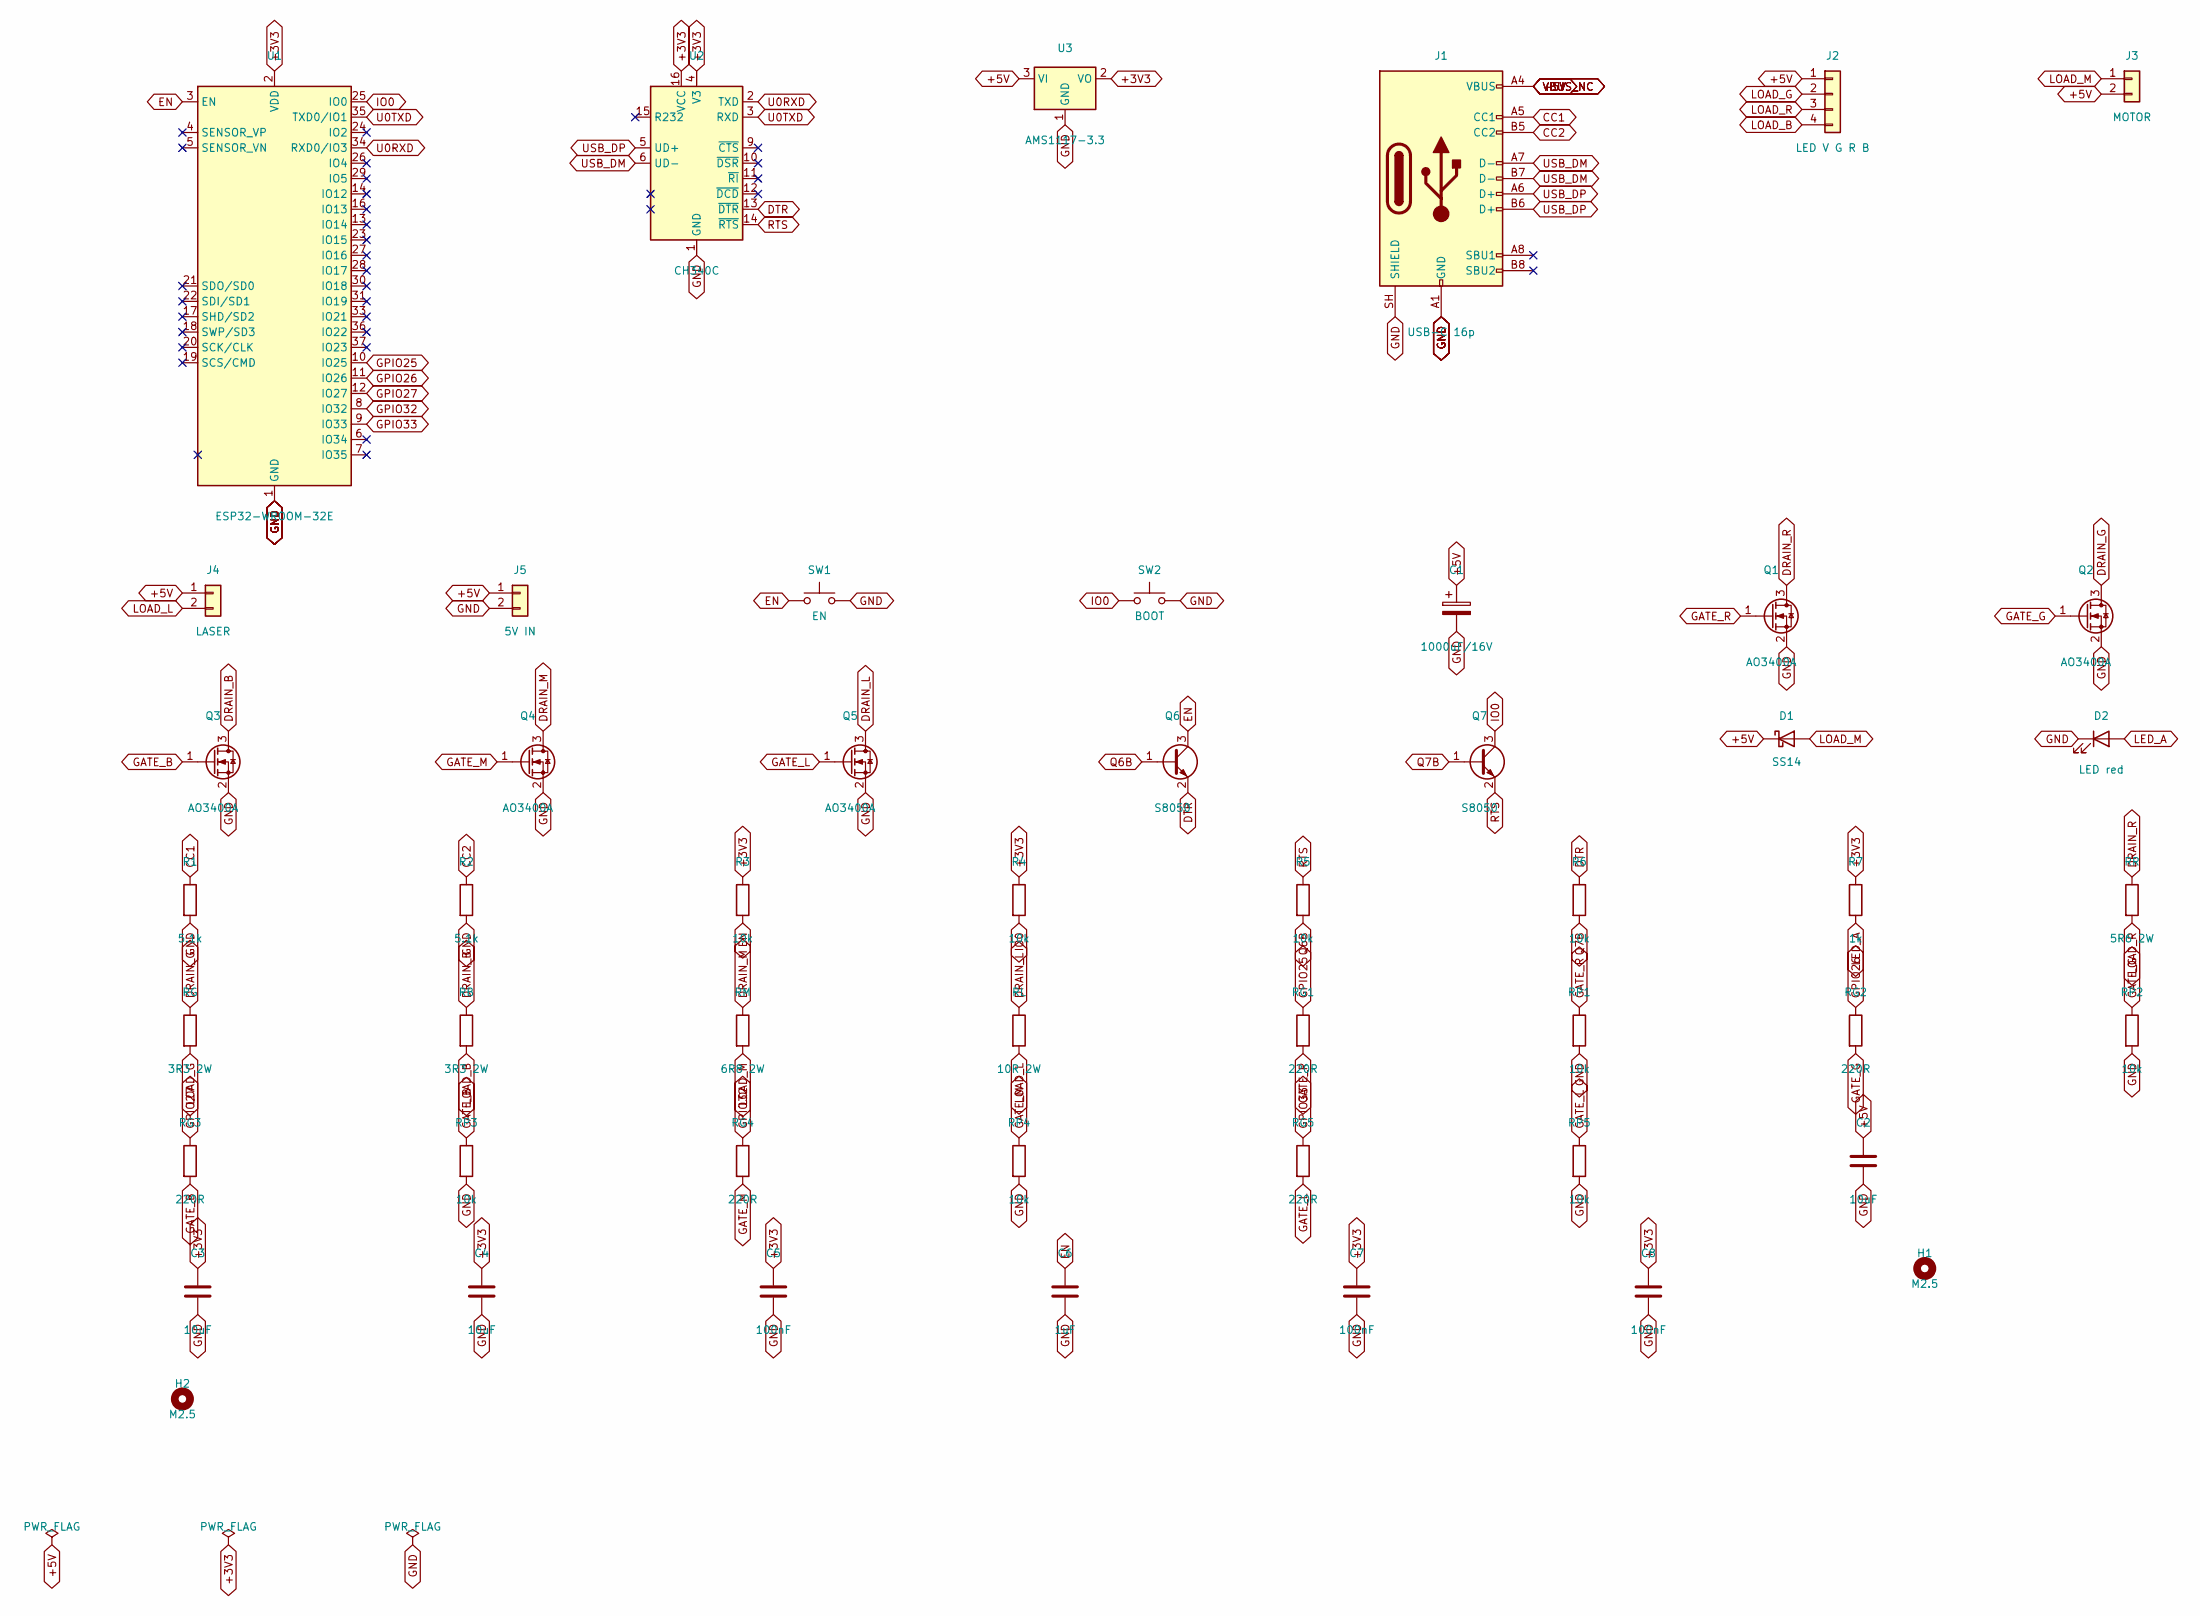
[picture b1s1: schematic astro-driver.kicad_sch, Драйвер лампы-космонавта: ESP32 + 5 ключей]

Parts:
C1: 1000uF/16V; CP_Radial_D10.0mm_P5.00mm
C2, C3, C4: 10uF; C_0805_2012Metric; LCSC C15850
C5, C7, C8: 100nF; C_0603_1608Metric; LCSC C14663
C6: 1uF; C_0603_1608Metric; LCSC C15849
D1: SS14; D_SMA; LCSC C2480
D2: LED red; LED_0603_1608Metric; LCSC C2286
H1, H2: M2.5; MountingHole_2.7mm_M2.5
J1: USB-C 16p; USB_C_Receptacle_HRO_TYPE-C-31-M-12; LCSC C165948
J2: LED V G R B; PinHeader_1x04_P2.54mm_Vertical
J3: MOTOR; PinHeader_1x02_P2.54mm_Vertical
J4: LASER; PinHeader_1x02_P2.54mm_Vertical
J5: 5V IN; PinHeader_1x02_P2.54mm_Vertical
Q1, Q2, Q3, Q4, Q5: AO3400A; SOT-23; LCSC C20917
Q6, Q7: S8050; SOT-23; LCSC C2146
R1, R2: 5.1k; R_0603_1608Metric; LCSC C23186
R3, R4, R5, R6: 10k; R_0603_1608Metric; LCSC C25804
R7: 1k; R_0603_1608Metric; LCSC C21190
RB: 3R3 2W; R_Axial_DIN0414_L11.9mm_D4.5mm_P15.24mm_Horizontal
RG: 3R3 2W; R_Axial_DIN0414_L11.9mm_D4.5mm_P15.24mm_Horizontal
RG1, RG2, RG3, RG4, RG5: 220R; R_0603_1608Metric; LCSC C22962
RL: 10R 2W; R_Axial_DIN0414_L11.9mm_D4.5mm_P15.24mm_Horizontal
RM: 6R8 2W; R_Axial_DIN0414_L11.9mm_D4.5mm_P15.24mm_Horizontal
RP1, RP2, RP3, RP4, RP5: 10k; R_0603_1608Metric; LCSC C25804
RR: 5R6 2W; R_Axial_DIN0414_L11.9mm_D4.5mm_P15.24mm_Horizontal
SW1: EN; SW_PUSH_6mm
SW2: BOOT; SW_PUSH_6mm
U1: ESP32-WROOM-32E; ESP32-WROOM-32_body; LCSC C701341
U2: CH340C; SOIC-16_3.9x9.9mm_P1.27mm; LCSC C84681
U3: AMS1117-3.3; SOT-223-3_TabPin2; LCSC C6186

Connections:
+3V3: C3.1, C4.1, C5.1, C7.1, C8.1, R3.1, R4.1, R7.1, U1.2 (VDD), U2.4 (V3), U2.16 (VCC), U3.2 (VO)
CC1: J1.A5 (CC1), R1.1
CC2: J1.B5 (CC2), R2.1
DRAIN_B: Q3.3 (D), RB.1
DRAIN_G: Q2.3 (D), RG.1
DRAIN_L: Q5.3 (D), RL.1
DRAIN_M: Q4.3 (D), RM.1
DRAIN_R: Q1.3 (D), RR.1
DTR: Q6.2 (E), R6.1, U2.13 (~DTR)
EN: C6.1, Q6.3 (C), R3.2, SW1.1, U1.3 (EN)
GATE_B: Q3.1 (G), RG3.2, RP3.1
GATE_G: Q2.1 (G), RG2.2, RP2.1
GATE_L: Q5.1 (G), RG5.2, RP5.1
GATE_M: Q4.1 (G), RG4.2, RP4.1
GATE_R: Q1.1 (G), RG1.2, RP1.1
GND: C1.2, C2.2, C3.2, C4.2, C5.2, C6.2, C7.2, C8.2, D2.1 (K), J1.A1 (GND), J1.A12 (GND), J1.B1 (GND), J1.B12 (GND), J1.SH (SHIELD), J5.2, Q1.2 (S), Q2.2 (S), Q3.2 (S), Q4.2 (S), Q5.2 (S), R1.2, R2.2, RP1.2, RP2.2, RP3.2, RP4.2, RP5.2, SW1.2, SW2.2, U1.1 (GND), U1.15 (GND), U1.38 (GND), U1.39 (GND), U2.1 (GND), U3.1 (GND)
GPIO25: RG1.1, U1.10 (IO25)
GPIO26: RG2.1, U1.11 (IO26)
GPIO27: RG3.1, U1.12 (IO27)
GPIO32: RG4.1, U1.8 (IO32)
GPIO33: RG5.1, U1.9 (IO33)
IO0: Q7.3 (C), R4.2, SW2.1, U1.25 (IO0)
LED_A: D2.2 (A), R7.2
LOAD_B: J2.4, RB.2
LOAD_G: J2.2, RG.2
LOAD_L: J4.2, RL.2
LOAD_M: D1.2 (A), J3.1, RM.2
LOAD_R: J2.3, RR.2
Q6B: Q6.1 (B), R5.2
Q7B: Q7.1 (B), R6.2
RTS: Q7.2 (E), R5.1, U2.14 (~RTS)
U0RXD: U1.34 (RXD0/IO3), U2.2 (TXD)
U0TXD: U1.35 (TXD0/IO1), U2.3 (RXD)
USB_DM: J1.A7 (D-), J1.B7 (D-), U2.6 (UD-)
USB_DP: J1.A6 (D+), J1.B6 (D+), U2.5 (UD+)

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
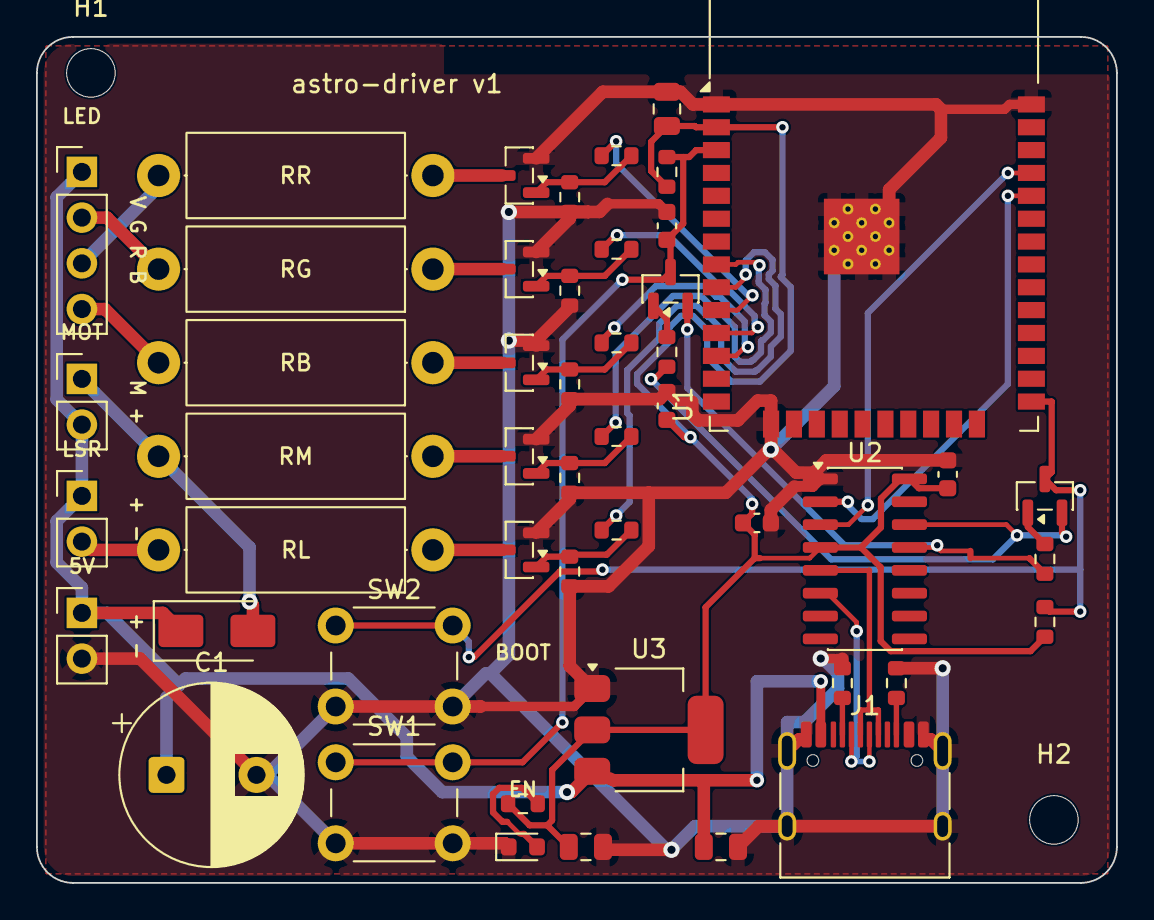
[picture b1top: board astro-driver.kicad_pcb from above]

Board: 2 copper layers, 60.0 x 47.0 mm, 51 parts (0 on the bottom side), 37 nets.

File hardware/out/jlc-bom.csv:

Comment,Designator,Footprint,LCSC Part #
10uF,"C2,C3,C4",C_0805_2012Metric,C15850
100nF,"C5,C7,C8",C_0603_1608Metric,C14663
1uF,C6,C_0603_1608Metric,C15849
SS14,D1,D_SMA,C2480
LED red,D2,LED_0603_1608Metric,C2286
USB-C 16p,J1,USB_C_Receptacle_HRO_TYPE-C-31-M-12,C165948
AO3400A,"Q1,Q2,Q3,Q4,Q5",SOT-23,C20917
S8050,"Q6,Q7",SOT-23,C2146
5.1k,"R1,R2",R_0603_1608Metric,C23186
10k,"R3,R4,R5,R6,RP1,RP2,RP3,RP4,RP5",R_0603_1608Metric,C25804
1k,R7,R_0603_1608Metric,C21190
220R,"RG1,RG2,RG3,RG4,RG5",R_0603_1608Metric,C22962
ESP32-WROOM-32E,U1,ESP32-WROOM-32_body,C701341
CH340C,U2,SOIC-16_3.9x9.9mm_P1.27mm,C84681
AMS1117-3.3,U3,SOT-223-3_TabPin2,C6186
